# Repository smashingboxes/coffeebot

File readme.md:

# Coffeebot

Coffeebot is an internet connected coffee timer that lets your office know when coffee has been made. The project uses a Particle Photon processor to drive an LCD that contains the time that the last coffee was brewed and send events to Slack via [IFTTT](https://ifttt.com/). The hardware is basically an internet-connected LCD with four buttons, and can be used for many uses outside of coffee.

Full design and code files can be found in this repo and a direct link to buy the board from OSHPark can be found at: https://oshpark.com/shared_projects/5fzQkFQy

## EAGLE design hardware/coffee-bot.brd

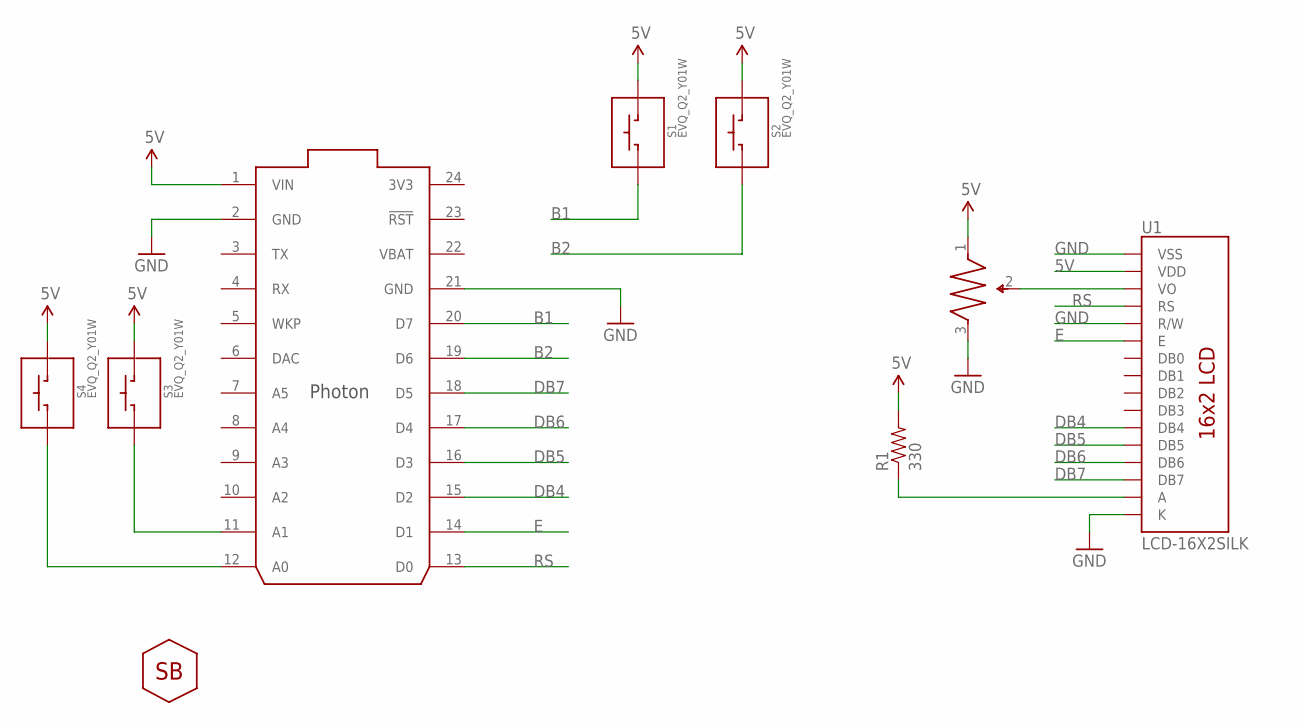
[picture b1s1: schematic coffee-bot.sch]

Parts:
R1: 330; 1206
S1, S2, S3, S4: EVQ_Q2_Y01W; EVQQ2
U1: LCD-16X2SILK; LCD-16X2
U2: PHOTON_SMD
U$2: TC-33X2
U$3: SBLOGO250MIL; SBLOGO

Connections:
3V3: U2.24 (3V3)
5V: R1.2, S1.B1 (B), S1.B2 (B), S2.B1 (B), S2.B2 (B), S3.B1 (B), S3.B2 (B), S4.B1 (B), S4.B2 (B), U1.2 (VDD), U2.1 (VIN), U$2.1
B1: S1.A1 (A), S1.A2 (A), U2.20 (D7)
B2: S2.A1 (A), S2.A2 (A), U2.19 (D6)
DB4: U1.11 (DB4), U2.15 (D2)
DB5: U1.12 (DB5), U2.16 (D3)
DB6: U1.13 (DB6), U2.17 (D4)
DB7: U1.14 (DB7), U2.18 (D5)
E: U1.6 (E), U2.14 (D1)
GND: U1.1 (VSS), U1.5 (R/W), U1.16 (K), U2.2 (GND), U2.21 (GND), U$2.3
unnamed: U1.3 (VO), U$2.2
unnamed: S4.A1 (A), S4.A2 (A), U2.12 (A0)
unnamed: S3.A1 (A), S3.A2 (A), U2.11 (A1)
unnamed: R1.1, U1.15 (A)
RS: U1.4 (RS), U2.13 (D0)
VBAT: U2.22 (VBAT)

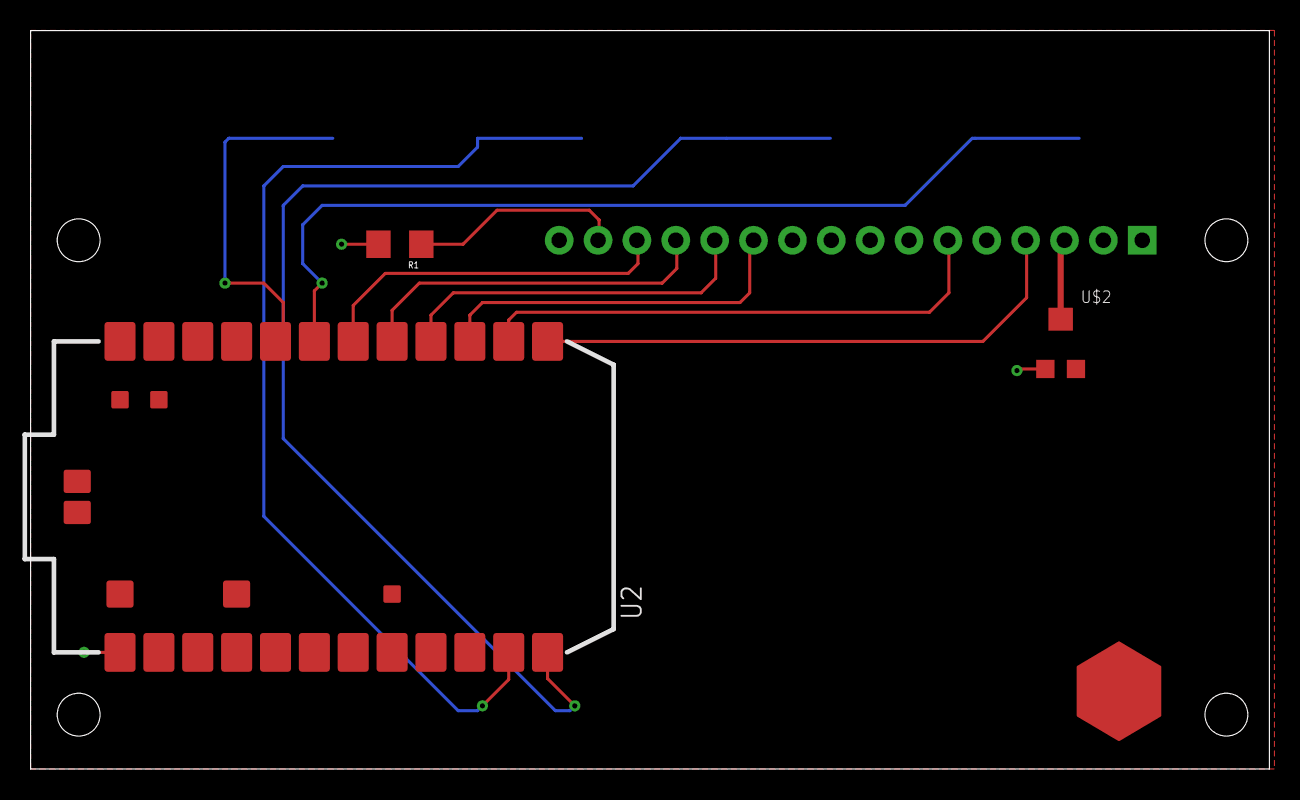
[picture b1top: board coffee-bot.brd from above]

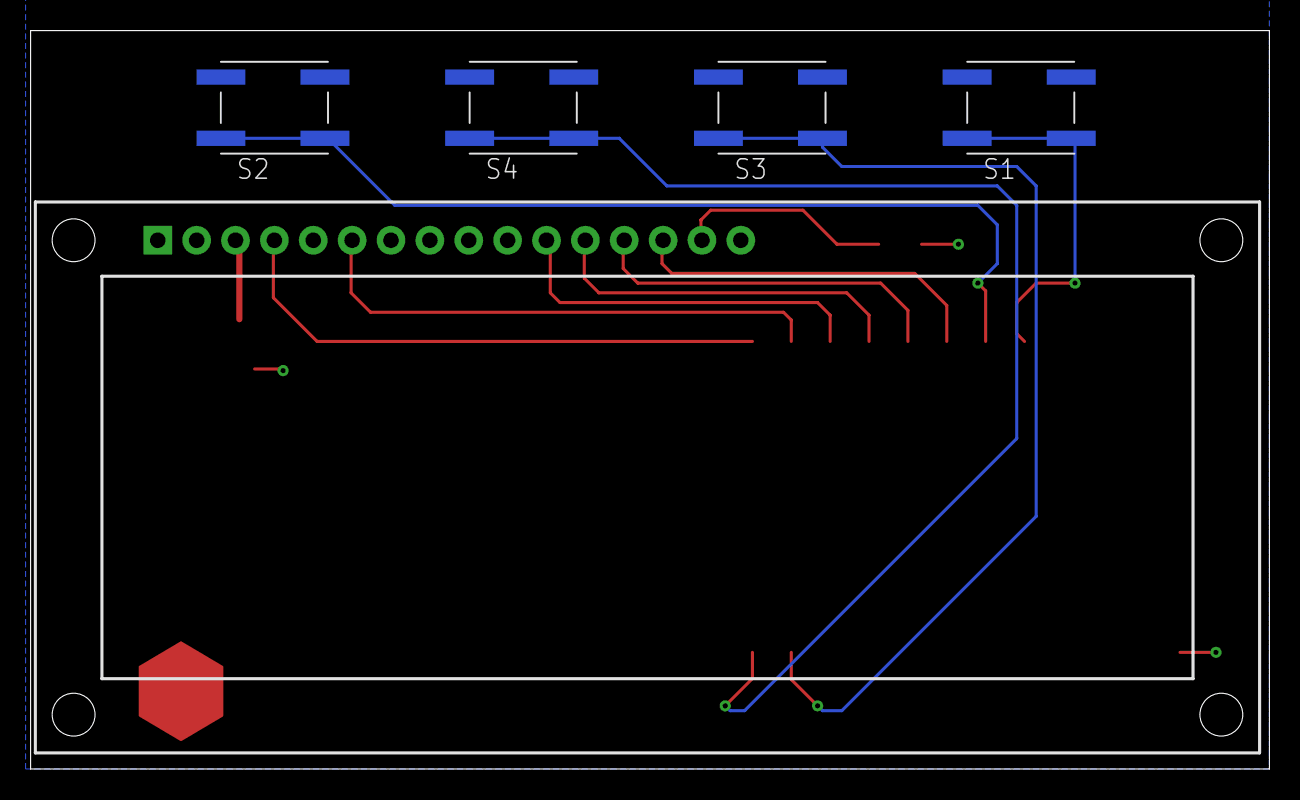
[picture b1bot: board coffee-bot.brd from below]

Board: 2 copper layers, 81.0 x 48.2 mm, 9 parts (5 on the bottom side), 14 nets.

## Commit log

2017-02-09 Initial commit.
2017-02-09 Fix 3D file extension.
2017-02-09 Remove .DS_Store files
2017-02-10 Updates coffeebot model and adds coffeebot back plate.

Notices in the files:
parts and their libraries:
SparkFun-Passives: Licensing: Creative Commons ShareAlike 4.0 International - https://creativecommons.org/licenses/by-sa/4.0
